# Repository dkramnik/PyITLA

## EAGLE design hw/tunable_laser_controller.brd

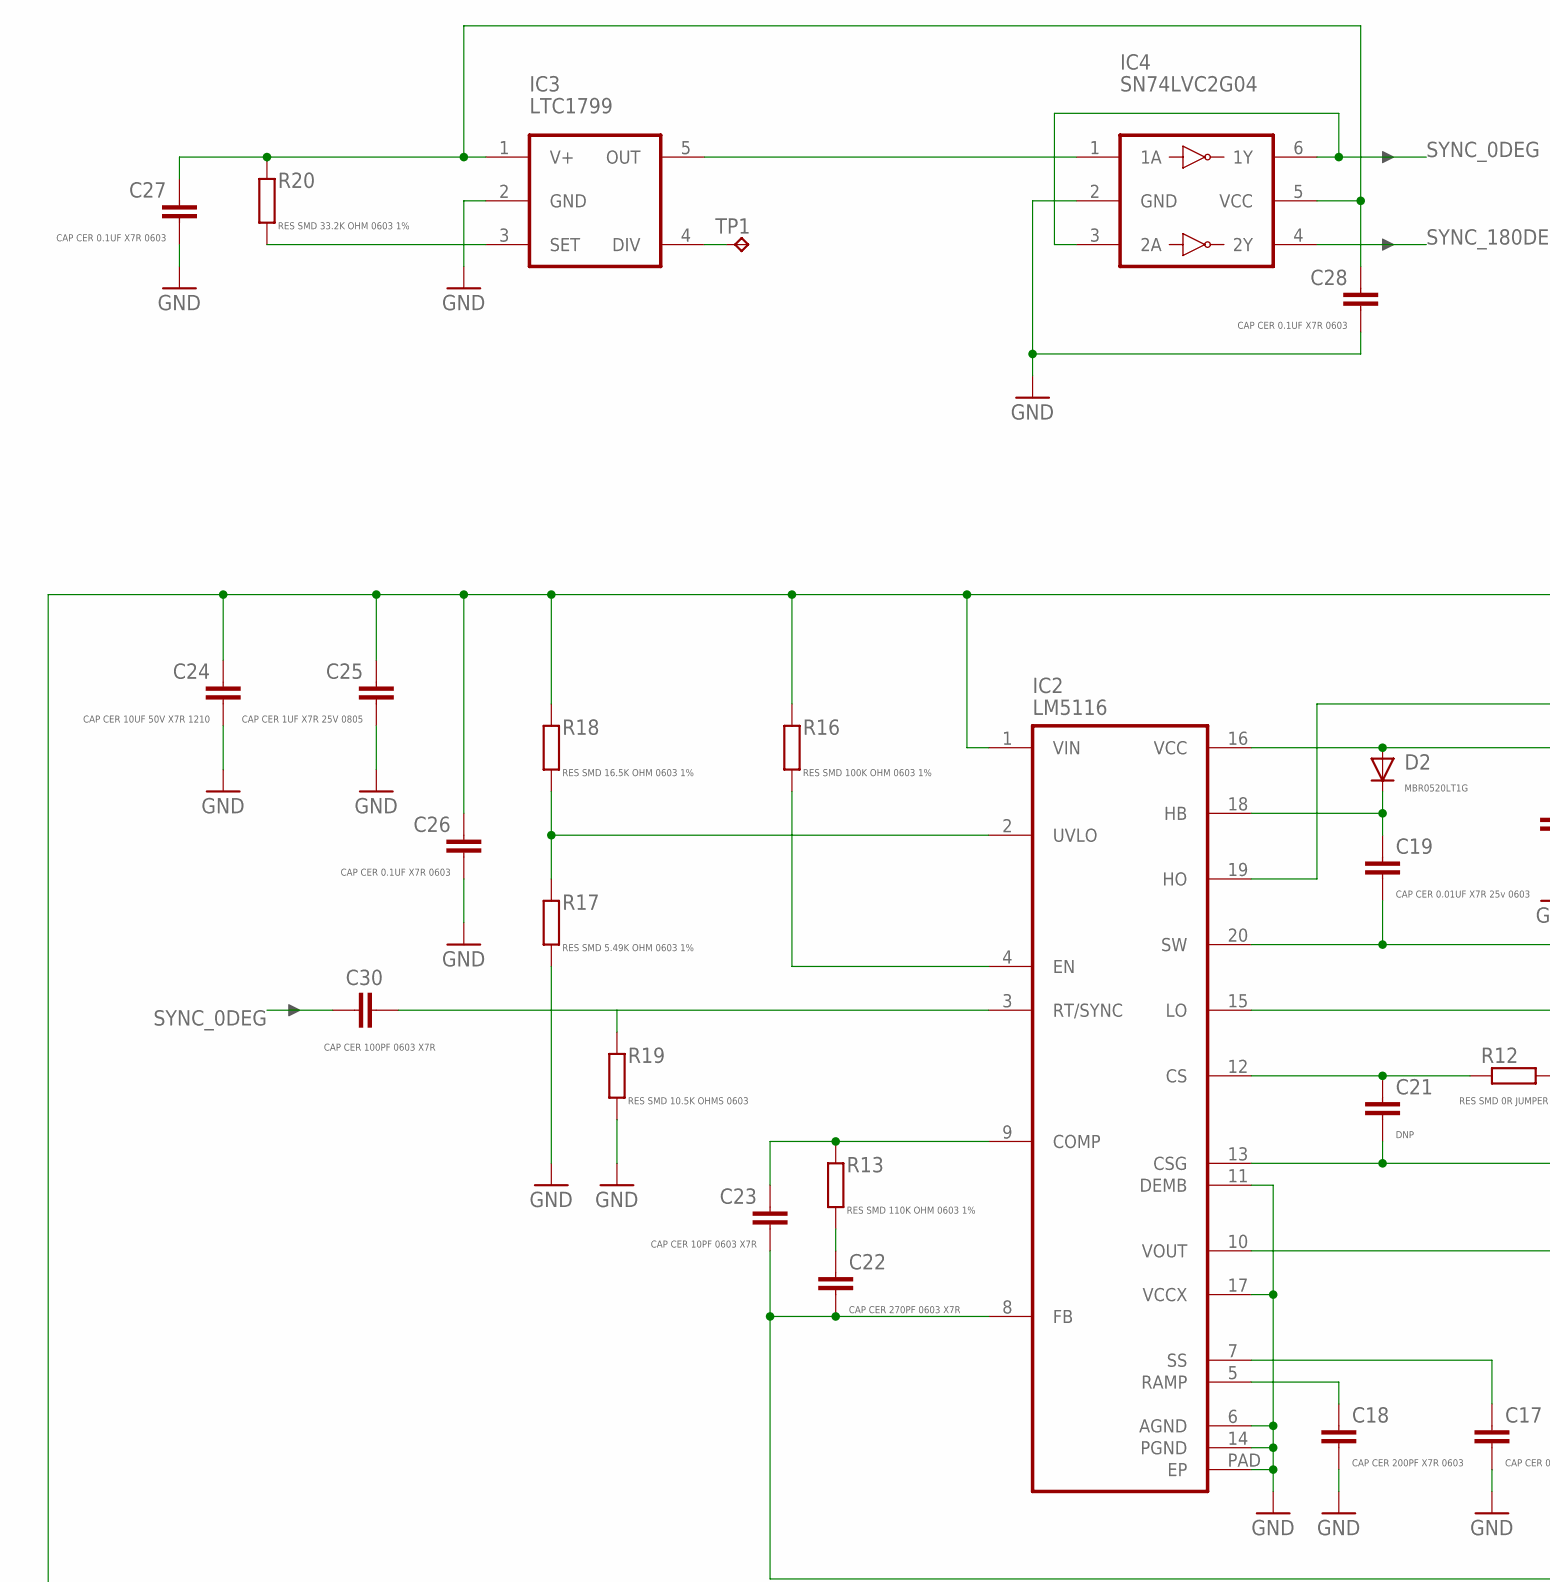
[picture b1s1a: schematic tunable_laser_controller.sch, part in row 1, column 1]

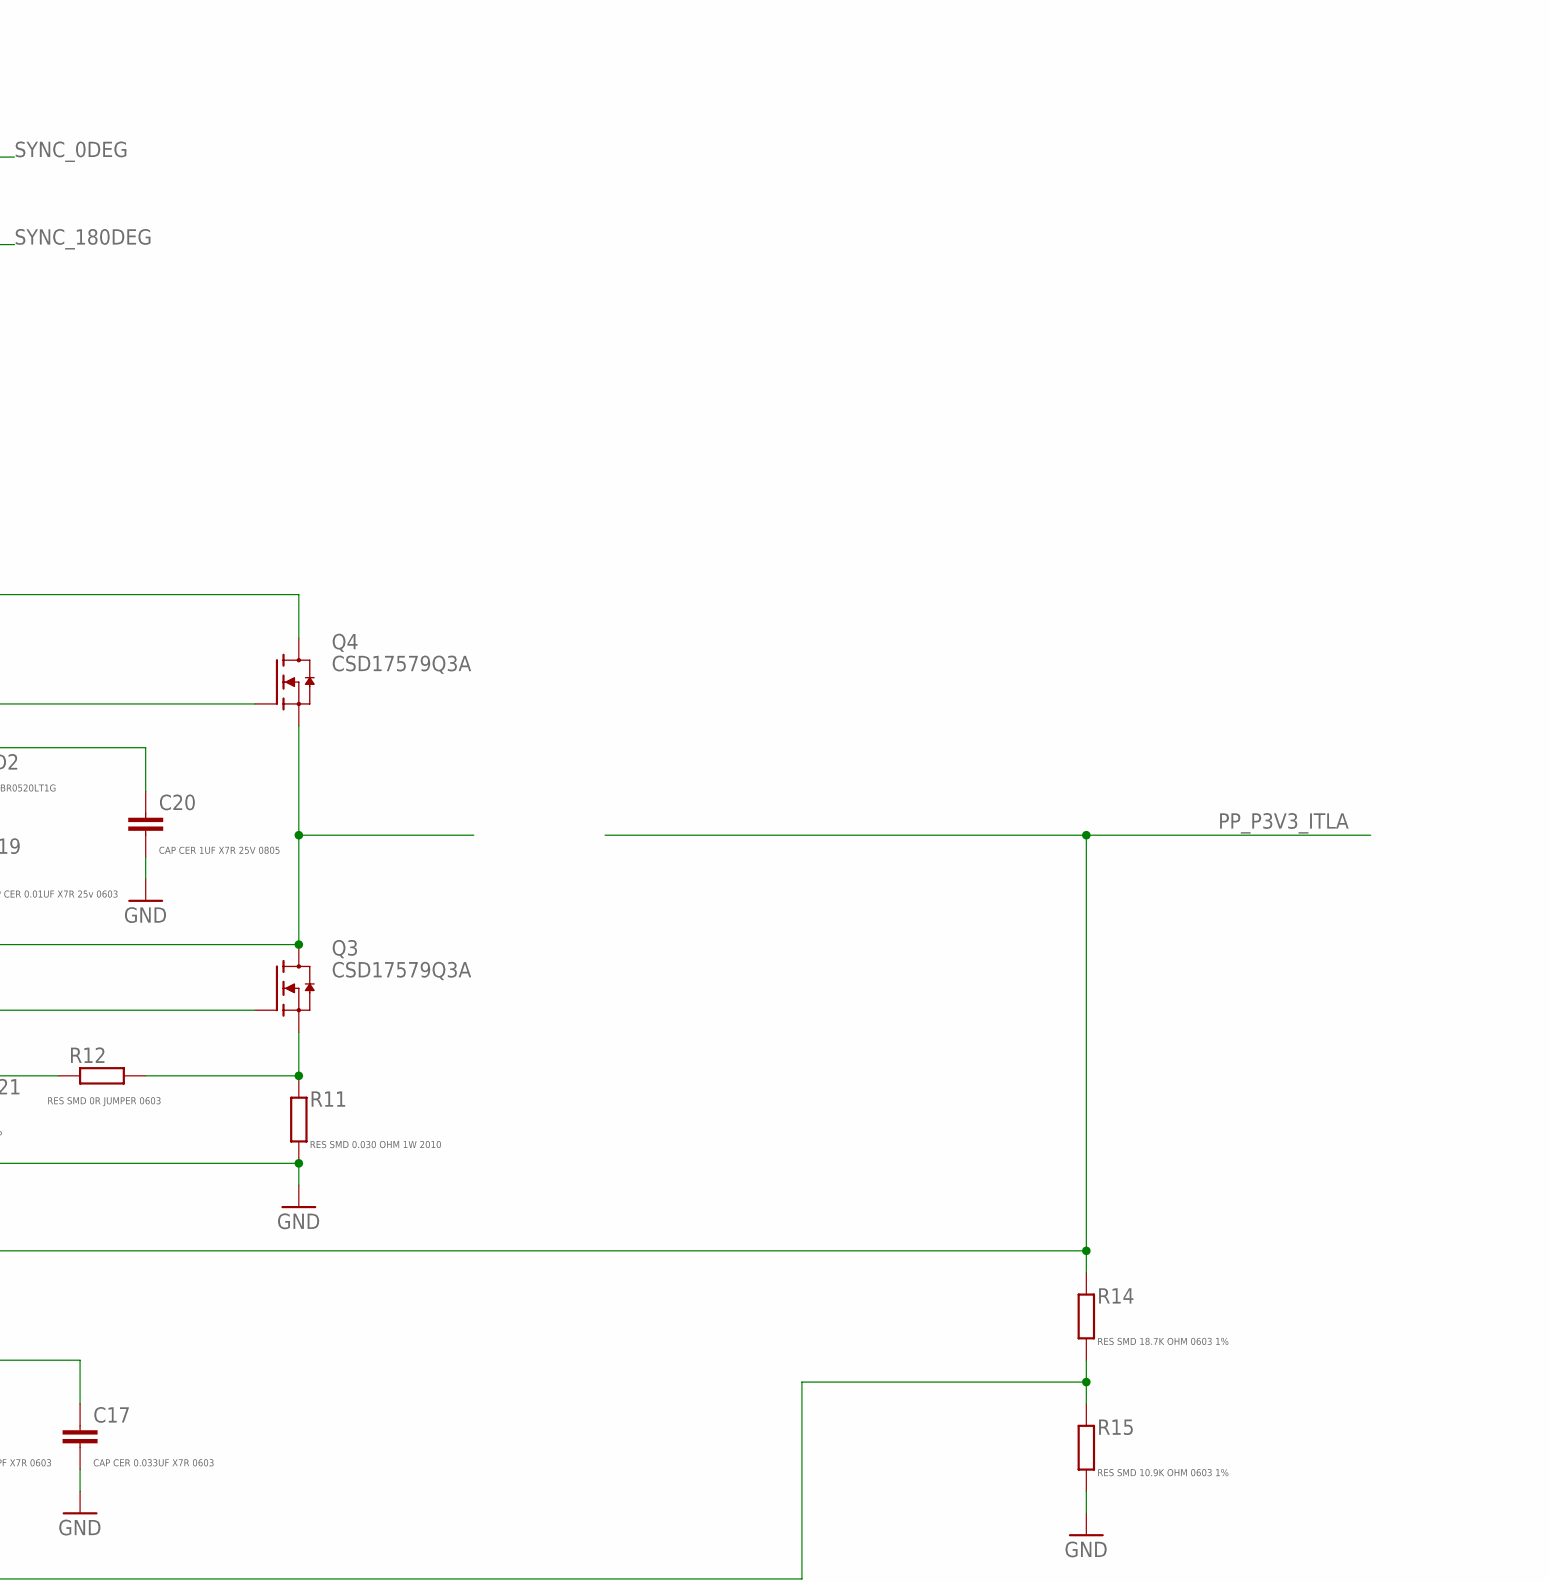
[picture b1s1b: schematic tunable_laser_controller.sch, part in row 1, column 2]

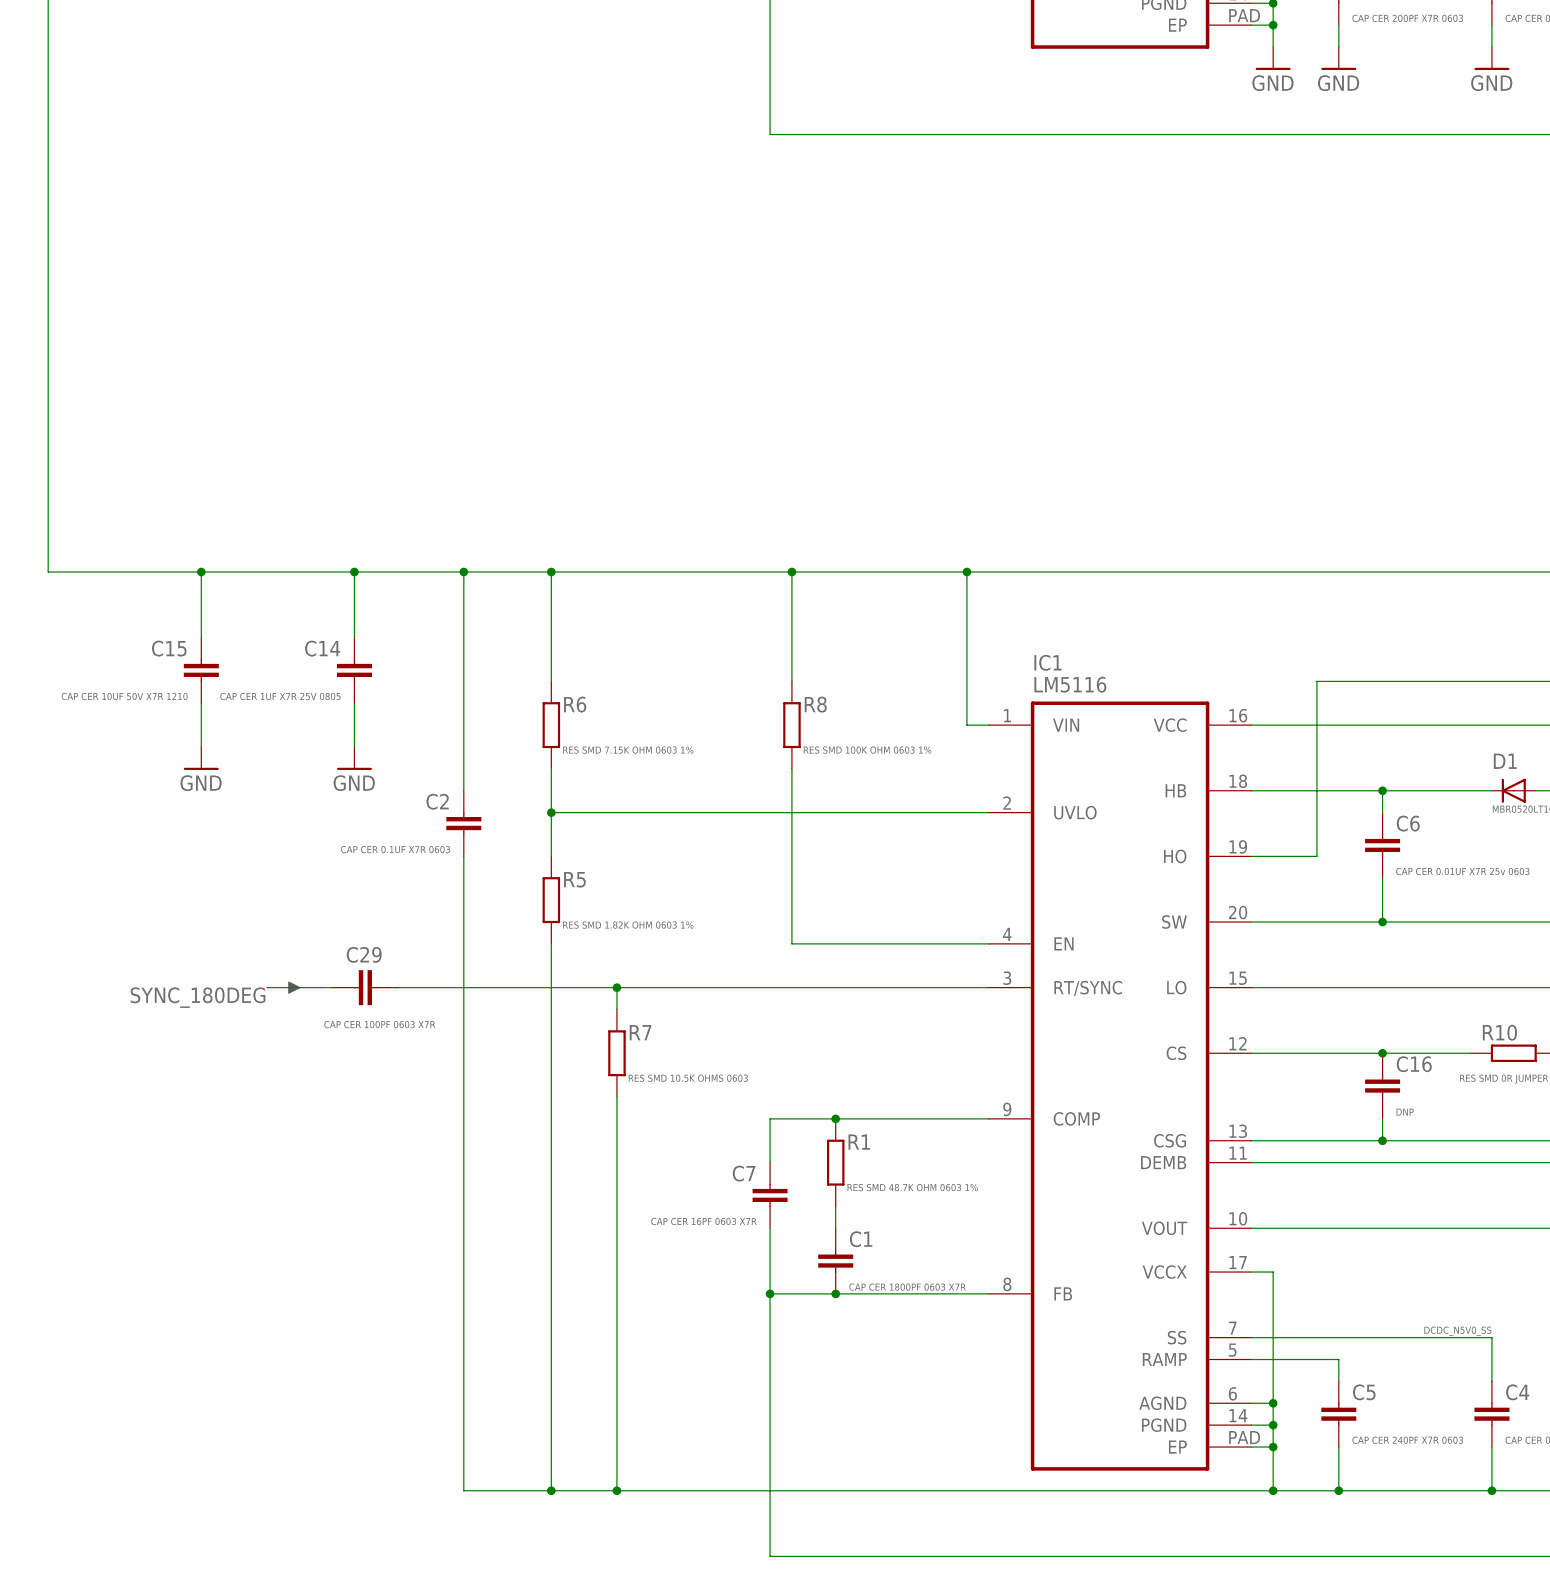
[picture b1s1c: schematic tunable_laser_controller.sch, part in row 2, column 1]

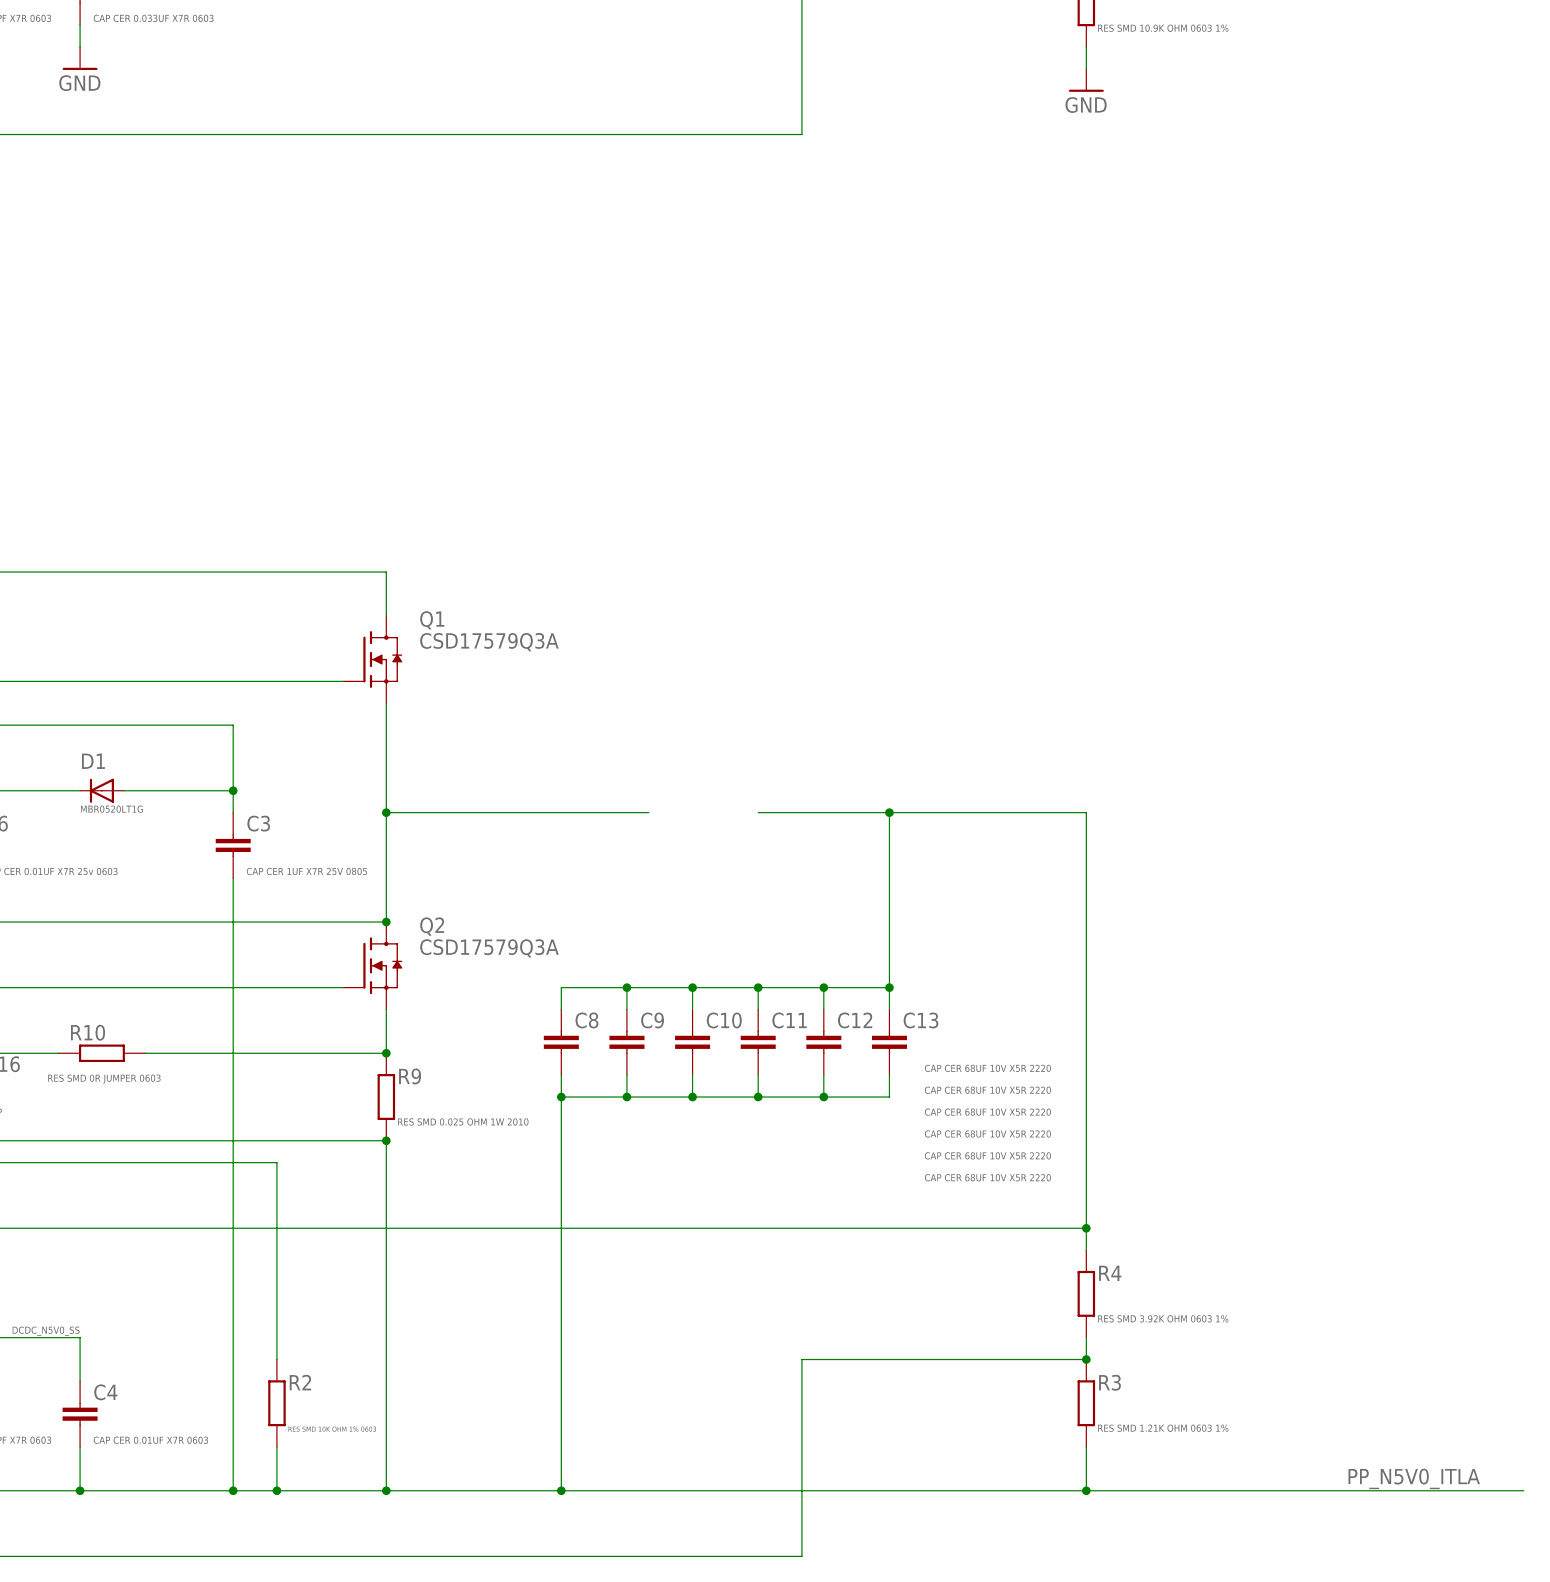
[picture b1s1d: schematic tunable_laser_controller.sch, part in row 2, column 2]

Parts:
C1: CAP CER 1800PF 0603 X7R; C0603
C2, C26, C27, C28: CAP CER 0.1UF X7R 0603; C0603
C3, C14, C20, C25: CAP CER 1UF X7R 25V 0805; C0805
C4: CAP CER 0.01UF X7R 0603; C0603
C5: CAP CER 240PF X7R 0603; C0603
C6, C19: CAP CER 0.01UF X7R 25v 0603; C0603
C7: CAP CER 16PF 0603 X7R; C0603
C8, C9, C10, C11, C12, C13: CAP CER 68UF 10V X5R 2220; C2220K
C15, C24: CAP CER 10UF 50V X7R 1210; C1210
C16, C21: DNP; C0603
C17: CAP CER 0.033UF X7R 0603; C0603
C18: CAP CER 200PF X7R 0603; C0603
C22: CAP CER 270PF 0603 X7R; C0603
C23: CAP CER 10PF 0603 X7R; C0603
C29, C30: CAP CER 100PF 0603 X7R; C0603
D1, D2: MBR0520LT1G; SOD-123_MINI-SMA
IC1, IC2: LM5116; TSSOP20-PAD
IC3: LTC1799; SOT23-5L
IC4: SN74LVC2G04; SOT23-6L
Q1, Q2, Q3, Q4: CSD17579Q3A; 8VSON
R1: RES SMD 48.7K OHM 0603 1%; R0603
R2: RES SMD 10K OHM 1% 0603; R0603
R3: RES SMD 1.21K OHM 0603 1%; R0603
R4: RES SMD 3.92K OHM 0603 1%; R0603
R5: RES SMD 1.82K OHM 0603 1%; R0603
R6: RES SMD 7.15K OHM 0603 1%; R0603
R7, R19: RES SMD 10.5K OHMS 0603; R0603
R8, R16: RES SMD 100K OHM 0603 1%; R0603
R9: RES SMD 0.025 OHM 1W 2010; R1210
R10, R12: RES SMD 0R JUMPER 0603; R0603
R11: RES SMD 0.030 OHM 1W 2010; R1210
R13: RES SMD 110K OHM 0603 1%; R0603
R14: RES SMD 18.7K OHM 0603 1%; R0603
R15: RES SMD 10.9K OHM 0603 1%; R0603
R17: RES SMD 5.49K OHM 0603 1%; R0603
R18: RES SMD 16.5K OHM 0603 1%; R0603
R20: RES SMD 33.2K OHM 0603 1%; R0603
TP1: TPTP20R; TP20R

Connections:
DCDC_N5V0_SS: C4.1, IC1.7 (SS)
GND: C14.2, C15.2, C17.2, C18.2, C20.2, C21.2, C24.2, C25.2, C26.2, C27.2, C28.2, IC2.6 (AGND), IC2.11 (DEMB), IC2.13 (CSG), IC2.14 (PGND), IC2.17 (VCCX), IC2.PAD (EP), IC3.2 (GND), IC4.2 (GND), R11.1, R15.1, R17.1, R19.1
unnamed: C1.1, R1.1
unnamed: C7.1, IC1.9 (COMP), R1.2
unnamed: C1.2, C7.2, IC1.8 (FB), R3.2, R4.1
unnamed: IC1.2 (UVLO), R5.2, R6.1
unnamed: C5.1, IC1.5 (RAMP)
unnamed: IC1.4 (EN), R8.2
unnamed: IC1.11 (DEMB), R2.2
unnamed: C6.1, D1.C, IC1.18 (HB)
unnamed: C6.2, IC1.20 (SW), Q1.1 (S), Q1.2 (S), Q1.3 (S), Q2.5 (D), Q2.6 (D), Q2.7 (D), Q2.8 (D), Q2.9 (D), Q2.V1 (D), Q2.V2 (D), Q2.V3 (D), Q2.V4 (D), Q2.V5 (D), Q2.V6 (D)
unnamed: C2.1, C14.1, C15.1, C24.1, C25.1, C26.1, IC1.1 (VIN), IC2.1 (VIN), Q1.5 (D), Q1.6 (D), Q1.7 (D), Q1.8 (D), Q1.9 (D), Q1.V1 (D), Q1.V2 (D), Q1.V3 (D), Q1.V4 (D), Q1.V5 (D), Q1.V6 (D), Q4.5 (D), Q4.6 (D), Q4.7 (D), Q4.8 (D), Q4.9 (D), Q4.V1 (D), Q4.V2 (D), Q4.V3 (D), Q4.V4 (D), Q4.V5 (D), Q4.V6 (D), R6.2, R8.1, R16.1, R18.2
unnamed: C16.1, IC1.12 (CS), R10.2
unnamed: IC1.19 (HO), Q1.4 (G)
unnamed: C19.1, D2.C, IC2.18 (HB)
unnamed: IC1.15 (LO), Q2.4 (G)
unnamed: C8.1, C9.1, C10.1, C11.1, C12.1, C13.1, IC1.10 (VOUT), R4.2
unnamed: C3.1, D1.A, IC1.16 (VCC)
unnamed: C29.2, IC1.3 (RT/SYNC), R7.2
unnamed: Q2.1 (S), Q2.2 (S), Q2.3 (S), R9.2, R10.1
unnamed: C18.1, IC2.5 (RAMP)
unnamed: C17.1, IC2.7 (SS)
unnamed: IC2.15 (LO), Q3.4 (G)
unnamed: C20.1, D2.A, IC2.16 (VCC)
unnamed: C21.1, IC2.12 (CS), R12.2
unnamed: IC2.19 (HO), Q4.4 (G)
unnamed: C19.2, IC2.20 (SW), Q3.5 (D), Q3.6 (D), Q3.7 (D), Q3.8 (D), Q3.9 (D), Q3.V1 (D), Q3.V2 (D), Q3.V3 (D), Q3.V4 (D), Q3.V5 (D), Q3.V6 (D), Q4.1 (S), Q4.2 (S), Q4.3 (S)
unnamed: Q3.1 (S), Q3.2 (S), Q3.3 (S), R11.2, R12.1
unnamed: C22.1, R13.1
unnamed: C23.1, IC2.9 (COMP), R13.2
unnamed: C22.2, C23.2, IC2.8 (FB), R14.1, R15.2
unnamed: IC2.2 (UVLO), R17.2, R18.1
unnamed: C30.2, IC2.3 (RT/SYNC), R19.2
unnamed: IC3.3 (SET), R20.2
unnamed: IC2.4 (EN), R16.2
unnamed: IC3.4 (DIV), TP1.TP
unnamed: IC3.5 (OUT), IC4.1 (1A)
unnamed: C27.1, C28.1, IC3.1 (V+), IC4.5 (VCC), R20.1
PP_N5V0_ITLA: C2.2, C3.2, C4.2, C5.2, C8.2, C9.2, C10.2, C11.2, C12.2, C13.2, C16.2, IC1.6 (AGND), IC1.13 (CSG), IC1.14 (PGND), IC1.17 (VCCX), IC1.PAD (EP), R2.1, R3.1, R5.1, R7.1, R9.1
PP_P3V3_ITLA: IC2.10 (VOUT), R14.2
SYNC_0DEG: C30.1, IC4.3 (2A), IC4.6 (1Y)
SYNC_180DEG: C29.1, IC4.4 (2Y)

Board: 2 copper layers, 61 parts (0 on the bottom side), 42 nets, no tracks yet.

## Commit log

2021-06-07 work on schematic
